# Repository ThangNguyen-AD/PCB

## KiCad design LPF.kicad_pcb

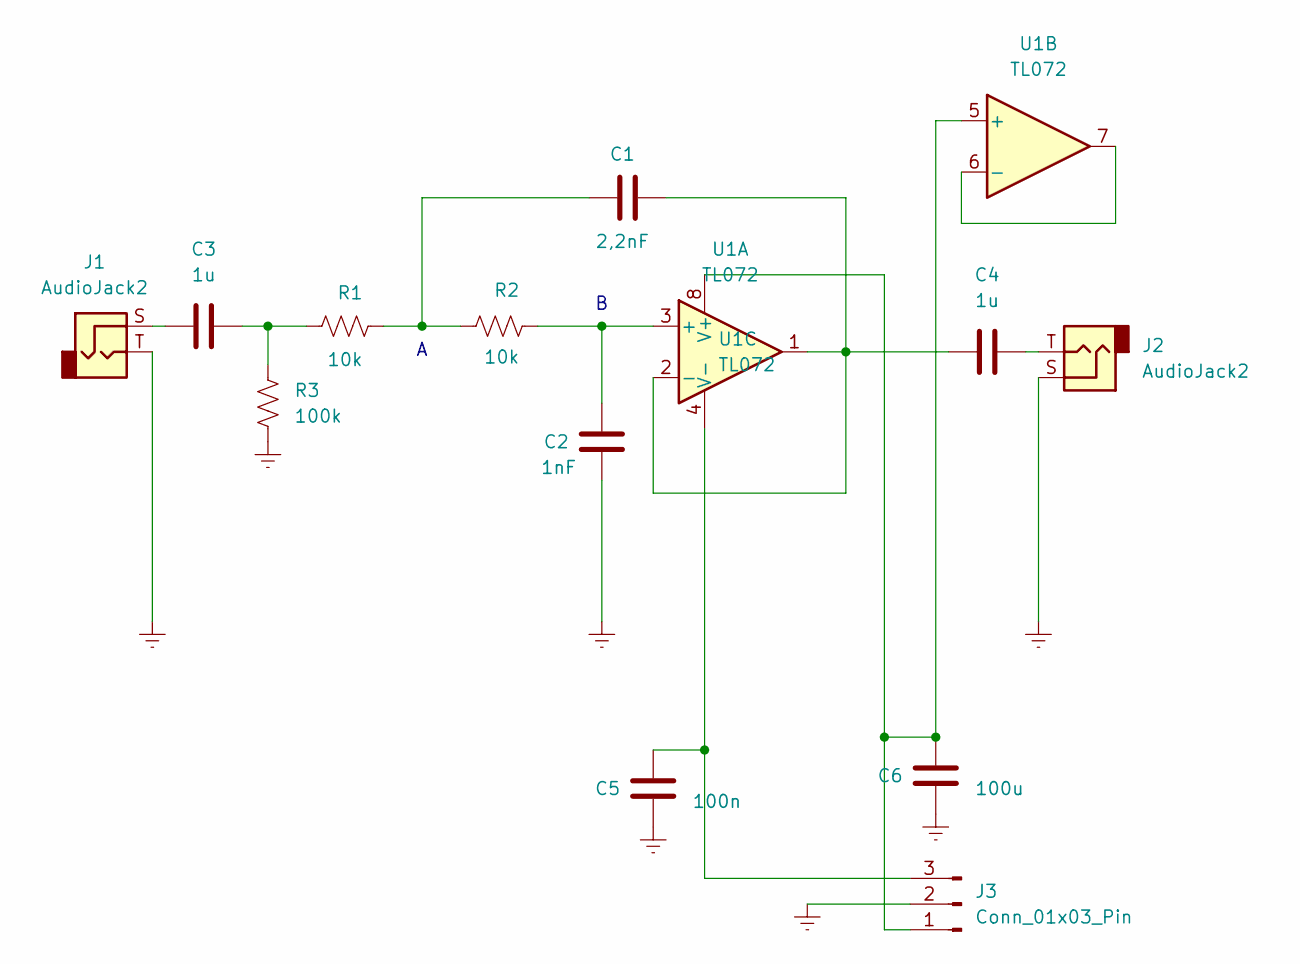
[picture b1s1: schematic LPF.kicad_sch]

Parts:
C1: 2,2nF; C_0805_2012Metric
C2: 1nF; C_0805_2012Metric
C3, C4: 1u; C_0805_2012Metric
C5: 100n; C_0805_2012Metric
C6: 100u; C_0805_2012Metric
J1, J2: AudioJack2; Jack_3.5mm_PJ320D_Horizontal
J3: Conn_01x03_Pin; PinHeader_1x03_P2.54mm_Horizontal
R1, R2: 10k; R_Axial_DIN0207_L6.3mm_D2.5mm_P10.16mm_Horizontal
R3: 100k; R_Axial_DIN0207_L6.3mm_D2.5mm_P10.16mm_Horizontal
U1: TL072; DIP-8_W7.62mm

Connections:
GNDREF: C2.2, C5.2, C6.2, J1.T, J2.S, J3.2, R3.2
unnamed: C1.1, R1.2, R2.1
unnamed: C3.1, J1.S
unnamed: C3.2, R1.1, R3.1
unnamed: C4.2, J2.T
unnamed: C6.1, J3.1, U1.5 (+), U1.8 (V+)
unnamed: C5.1, J3.3, U1.4 (V-)
unnamed: C2.1, R2.2, U1.3 (+)
unnamed: C1.2, C4.1, U1.1, U1.2 (-)
unnamed: U1.6 (-), U1.7

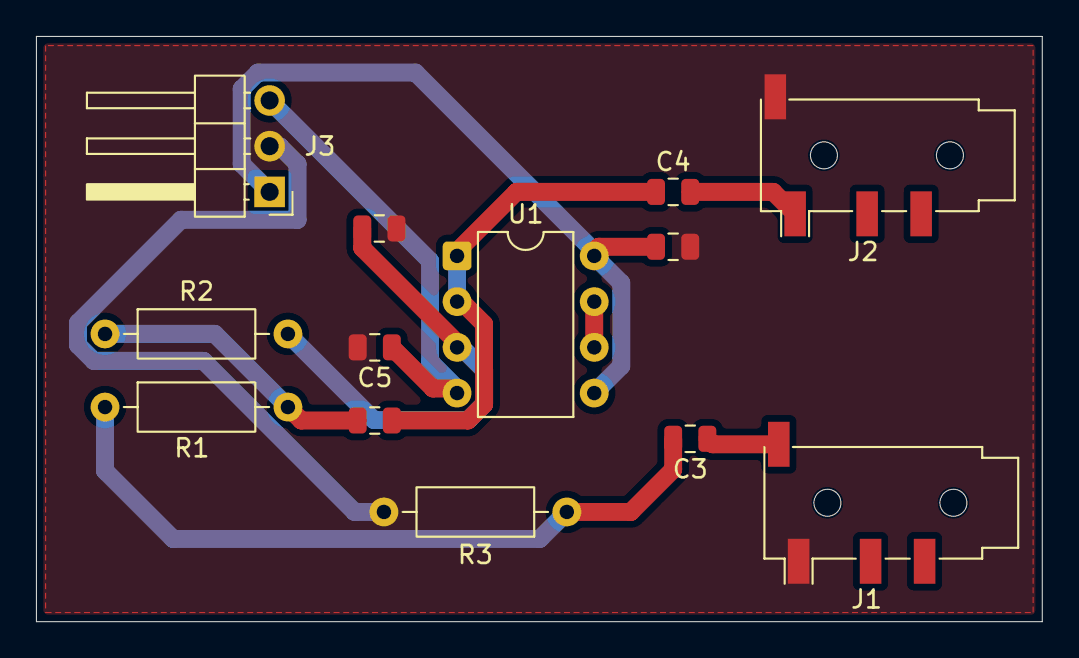
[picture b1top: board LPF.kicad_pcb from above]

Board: 2 copper layers, 55.9 x 32.5 mm, 13 parts (0 on the bottom side), 10 nets.
